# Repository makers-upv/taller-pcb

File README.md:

# taller-pcb
Taller introducción a la fabricación casera de circuitos impresos con materiales corrientes.

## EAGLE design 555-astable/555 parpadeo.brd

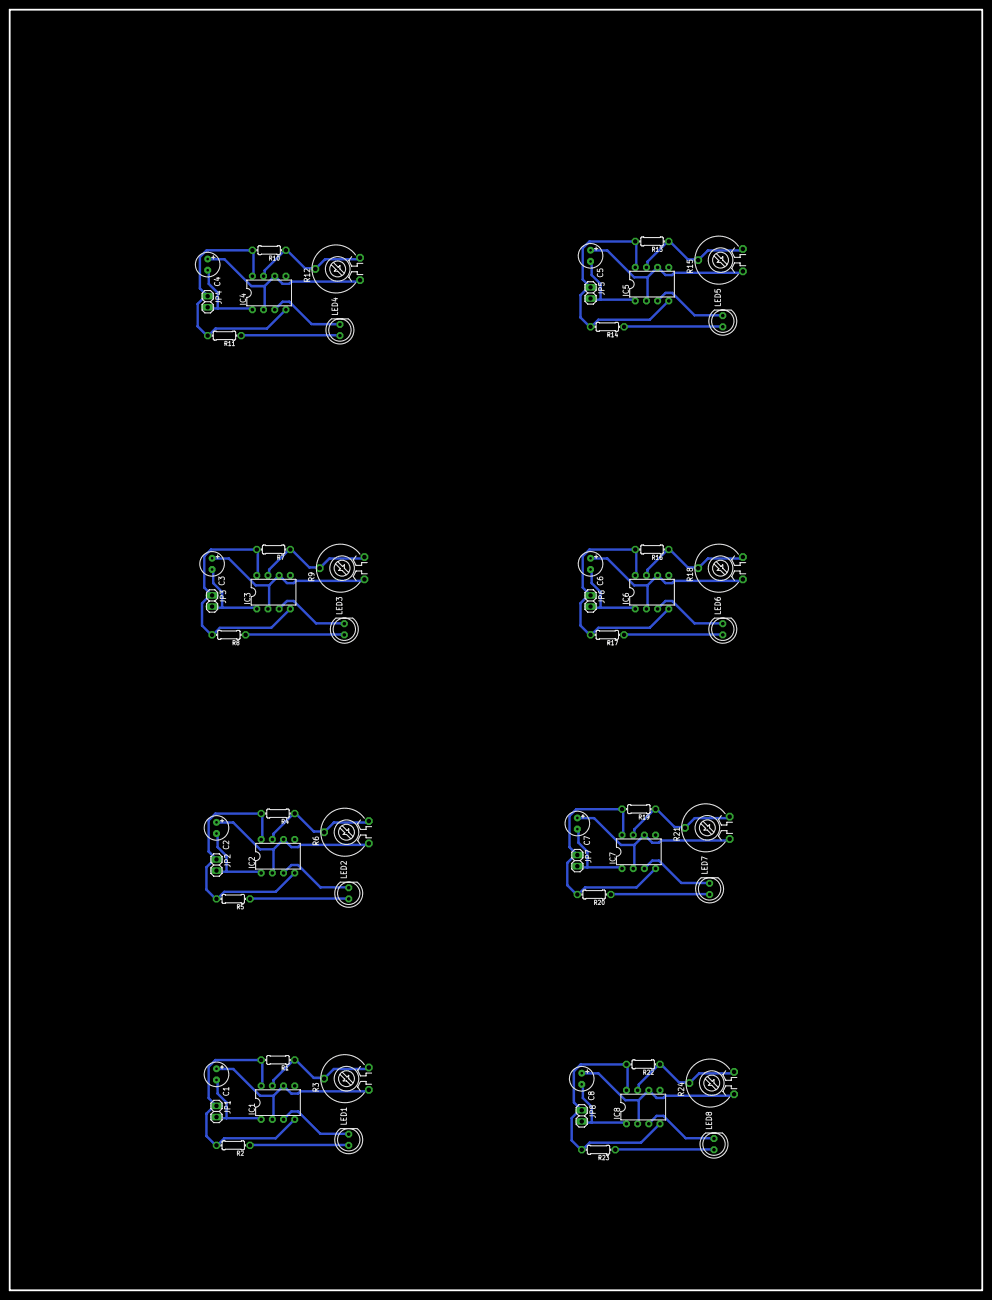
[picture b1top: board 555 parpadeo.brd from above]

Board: 2 copper layers, 221.0 x 291.0 mm, 56 parts (0 on the bottom side), 48 nets.

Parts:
C1, C2, C3, C4, C5, C6, C7, C8: 10u; E2,5-6
IC1, IC2, IC3, IC4, IC5, IC6, IC7, IC8: LM555N; DIL08
JP1, JP2, JP3, JP4, JP5, JP6, JP7, JP8: 1X02
LED1, LED2, LED3, LED4, LED5, LED6, LED7, LED8: LED5MM
R1, R4, R7, R10, R13, R16, R19, R22: 100k; 0204/7
R2, R5, R8, R11, R14, R17, R20, R23: 330; 0204/7
R3, R6, R9, R12, R15, R18, R21, R24: 100k; PT-10

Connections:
GND: C1.-, IC1.1, JP1.2
GND2: C2.-, IC2.1, JP2.2
GND3: C3.-, IC3.1, JP3.2
GND4: C4.-, IC4.1, JP4.2
GND5: C5.-, IC5.1, JP5.2
GND6: C6.-, IC6.1, JP6.2
GND7: C7.-, IC7.1, JP7.2
GND8: C8.-, IC8.1, JP8.2
unnamed: IC1.3, LED1.K
unnamed: LED1.A, R2.1
unnamed: IC1.7, R1.1, R3.2, R3.3
unnamed: C1.+, IC1.2, IC1.6, R3.1
unnamed: IC2.3, LED2.K
unnamed: LED2.A, R5.1
unnamed: IC2.7, R4.1, R6.2, R6.3
unnamed: C2.+, IC2.2, IC2.6, R6.1
unnamed: IC3.3, LED3.K
unnamed: LED3.A, R8.1
unnamed: IC3.7, R7.1, R9.2, R9.3
unnamed: C3.+, IC3.2, IC3.6, R9.1
unnamed: IC4.3, LED4.K
unnamed: LED4.A, R11.1
unnamed: IC4.7, R10.1, R12.2, R12.3
unnamed: C4.+, IC4.2, IC4.6, R12.1
unnamed: IC5.3, LED5.K
unnamed: LED5.A, R14.1
unnamed: IC5.7, R13.1, R15.2, R15.3
unnamed: C5.+, IC5.2, IC5.6, R15.1
unnamed: IC6.3, LED6.K
unnamed: LED6.A, R17.1
unnamed: IC6.7, R16.1, R18.2, R18.3
unnamed: C6.+, IC6.2, IC6.6, R18.1
unnamed: IC7.3, LED7.K
unnamed: LED7.A, R20.1
unnamed: IC7.7, R19.1, R21.2, R21.3
unnamed: C7.+, IC7.2, IC7.6, R21.1
unnamed: IC8.3, LED8.K
unnamed: LED8.A, R23.1
unnamed: IC8.7, R22.1, R24.2, R24.3
unnamed: C8.+, IC8.2, IC8.6, R24.1
VCC: IC1.4, IC1.8, JP1.1, R1.2, R2.2
VCC2: IC2.4, IC2.8, JP2.1, R4.2, R5.2
VCC3: IC3.4, IC3.8, JP3.1, R7.2, R8.2
VCC4: IC4.4, IC4.8, JP4.1, R10.2, R11.2
VCC5: IC5.4, IC5.8, JP5.1, R13.2, R14.2
VCC6: IC6.4, IC6.8, JP6.1, R16.2, R17.2
VCC7: IC7.4, IC7.8, JP7.1, R19.2, R20.2
VCC8: IC8.4, IC8.8, JP8.1, R22.2, R23.2

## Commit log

2017-06-03 Added 555-doorbell
2017-06-03 Added 555-astable folder
2017-06-03 Added PDFs, slides and 555-stable
2017-06-03 Added schematic, links modified
